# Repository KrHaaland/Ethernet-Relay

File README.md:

# Ethernet-Relay
Relay module using ethernet and MQTT

Put togethet with parts i had laying around.

Its based on a Atmega328p using minicore Arduino bootloader, running at 8Mhz at 3.3 volts.

Ethernet is a W5500-module brought from aliexpress, a 24LC512 for storing the web-interface, FT232 for communicating via usb and updating FW.

The mqtt topic postfix is "/relay1/set" and "/relay2/set" for turing the relays on or off, and "/relay1" or "/relay2" for getting the current status of the relays, the staus will be published according to update time set in the web-interface.

PCB is drawn in Kicad and the casing is draw using solidworks and printed on a Prusa mini+ 3D-Printer.
The print has inserts melted in place to have threads, used for fasten pcb and the back lid.

Some Instructions, the external EEPROM is written by a seperate program, since the controller is to small to contain the web page while running the primary program. When the EEPROM is written the primary program is uploaded and are using the data on the EEPROM to send the web page to a web-client request.

The FT232 is default set to 100mA, this might not be a problem if the device is powered by a charger, but beeing powered by the USB of a computer 100mA is not enough to power the ethernet or relays, this is solved using [FT_PROG](https://ftdichip.com/utilities/) to configure the FT232 to be able to draw up to 500mA.

</br><br></br><br></br><br>

</br><br></br><br></br><br>

</br><br></br><br></br><br>

</br><br></br><br></br><br>

</br><br></br><br></br><br>

</br><br></br><br></br><br>

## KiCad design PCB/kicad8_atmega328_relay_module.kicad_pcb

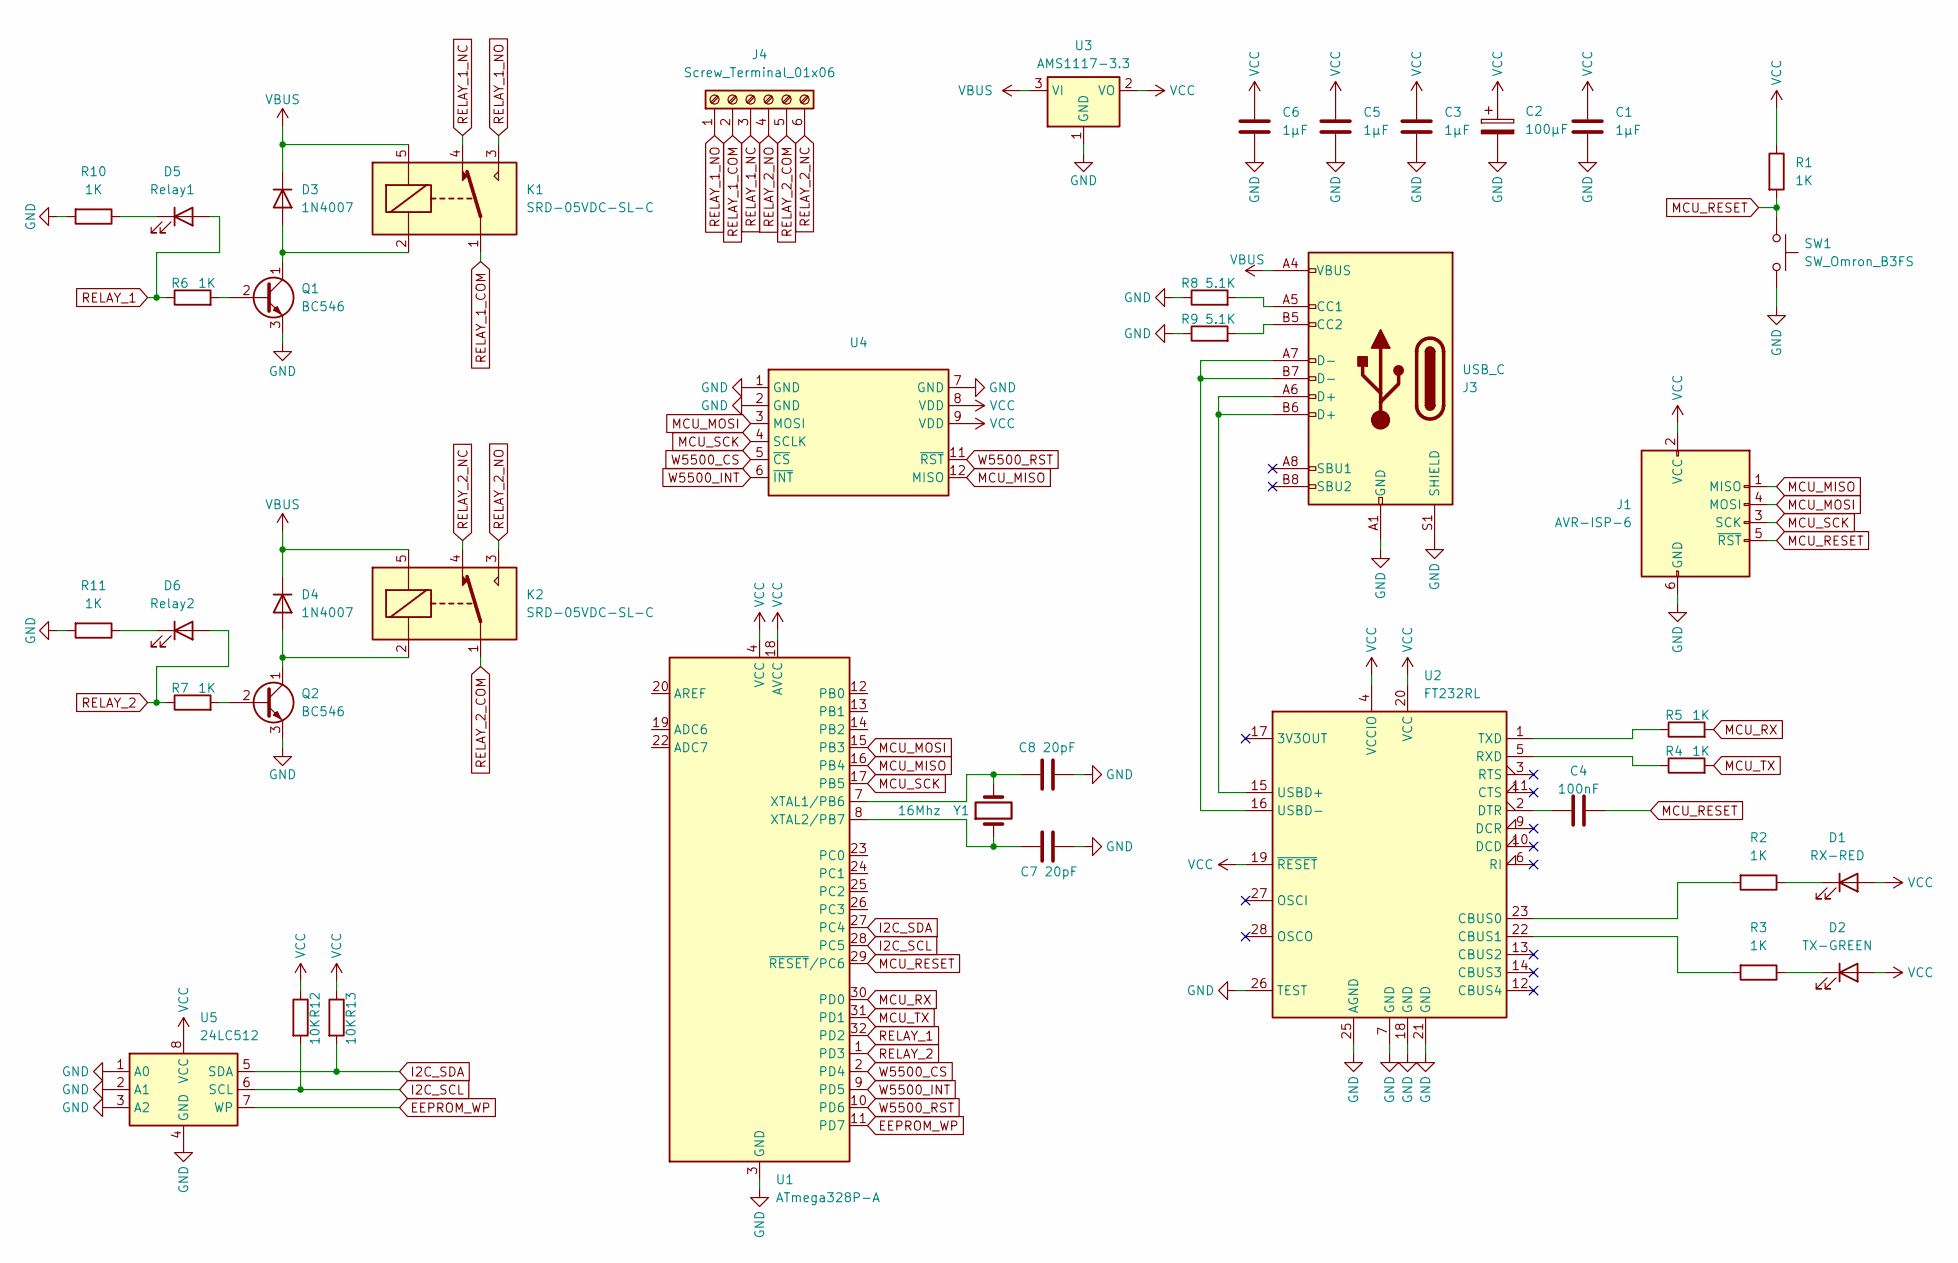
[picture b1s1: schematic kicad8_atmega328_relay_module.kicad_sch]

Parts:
C1, C3, C5, C6: 1µF; C_1206_3216Metric_Pad1.33x1.80mm_HandSolder
C2: 100µF; CP_Elec_5x5.8
C4: 100nF; C_1206_3216Metric_Pad1.33x1.80mm_HandSolder
C7, C8: 20pF; C_1206_3216Metric_Pad1.33x1.80mm_HandSolder
D1: RX-RED; LED_1206_3216Metric_Pad1.42x1.75mm_HandSolder
D2: TX-GREEN; LED_1206_3216Metric_Pad1.42x1.75mm_HandSolder
D3, D4: 1N4007; D_DO-41_SOD81_P7.62mm_Horizontal
D5: Relay1; LED_1206_3216Metric_Pad1.42x1.75mm_HandSolder
D6: Relay2; LED_1206_3216Metric_Pad1.42x1.75mm_HandSolder
J1: AVR-ISP-6; IDC-Header_2x03_P2.54mm_Vertical
J3: USB_C; USB_C_Receptacle_GCT_USB4110
J4: Screw_Terminal_01x06; TerminalBlock_WAGO_804-106_1x06_P5.00mm_45Degree
K1, K2: SRD-05VDC-SL-C; Relay_SPDT_SANYOU_SRD_Series_Form_C
Q1, Q2: BC546; TO-92_Inline
R1, R2, R3, R4, R5, R6, R7, R10, R11: 1K; R_1206_3216Metric_Pad1.30x1.75mm_HandSolder
R8, R9: 5.1K; R_1206_3216Metric_Pad1.30x1.75mm_HandSolder
R12, R13: 10K; R_1206_3216Metric_Pad1.30x1.75mm_HandSolder
SW1: SW_Omron_B3FS; SW_SPST_Omron_B3FS-100xP
U1: ATmega328P-A; TQFP-32_7x7mm_P0.8mm
U2: FT232RL; SSOP-28_5.3x10.2mm_P0.65mm
U3: AMS1117-3.3; SOT-223-3_TabPin2
U4: W5500Mini
U5: 24LC512; SOIC-8_3.9x4.9mm_P1.27mm
Y1: 16Mhz; Crystal_HC49-4H_Vertical

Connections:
EEPROM_WP: U1.11 (PD7), U5.7 (WP)
GND: C1.2, C2.2, C3.2, C5.2, C6.2, C7.2, C8.2, J1.6 (GND), J3.A1 (GND), J3.A12 (GND), J3.B1 (GND), J3.B12 (GND), J3.S1 (SHIELD), Q1.3 (E), Q2.3 (E), R8.1, R9.1, R10.2, R11.2, SW1.2, U1.3 (GND), U1.5 (GND), U1.21 (GND), U2.7 (GND), U2.18 (GND), U2.21 (GND), U2.25 (AGND), U2.26 (TEST), U3.1 (GND), U4.1 (GND), U4.2 (GND), U4.7 (GND), U5.1 (A0), U5.2 (A1), U5.3 (A2), U5.4 (GND)
I2C_SCL: R12.2, U1.28 (PC5), U5.6 (SCL)
I2C_SDA: R13.2, U1.27 (PC4), U5.5 (SDA)
MCU_MISO: J1.1 (MISO), U1.16 (PB4), U4.12 (MISO)
MCU_MOSI: J1.4 (MOSI), U1.15 (PB3), U4.3 (MOSI)
MCU_RESET: C4.1, J1.5 (~RST), R1.2, SW1.1, U1.29 (~RESET/PC6)
MCU_RX: R5.2, U1.30 (PD0)
MCU_SCK: J1.3 (SCK), U1.17 (PB5), U4.4 (SCLK)
MCU_TX: R4.2, U1.31 (PD1)
unnamed: D1.1 (K), R2.1
unnamed: D2.1 (K), R3.1
unnamed: D3.2 (A), K1.2, Q1.1 (C)
unnamed: D4.2 (A), K2.2, Q2.1 (C)
unnamed: D5.1 (K), R10.1
unnamed: D6.1 (K), R11.1
unnamed: J3.A5 (CC1), R8.2
unnamed: J3.B5 (CC2), R9.2
unnamed: Q1.2 (B), R6.2
unnamed: Q2.2 (B), R7.2
unnamed: C8.1, U1.7 (XTAL1/PB6), Y1.2
unnamed: C7.1, U1.8 (XTAL2/PB7), Y1.1
unnamed: R2.2, U2.23 (CBUS0)
unnamed: R3.2, U2.22 (CBUS1)
unnamed: C4.2, U2.2 (DTR)
unnamed: R4.1, U2.5 (RXD)
unnamed: R5.1, U2.1 (TXD)
RELAY_1: D5.2 (A), R6.1, U1.32 (PD2)
RELAY_1_COM: J4.2, K1.1
RELAY_1_NC: J4.3, K1.4
RELAY_1_NO: J4.1, K1.3
RELAY_2: D6.2 (A), R7.1, U1.1 (PD3)
RELAY_2_COM: J4.5, K2.1
RELAY_2_NC: J4.6, K2.4
RELAY_2_NO: J4.4, K2.3
USB_D+: J3.A6 (D+), J3.B6 (D+), U2.15 (USBD+)
USB_D-: J3.A7 (D-), J3.B7 (D-), U2.16 (USBD-)
VBUS: D3.1 (K), D4.1 (K), J3.A4 (VBUS), J3.A9 (VBUS), J3.B4 (VBUS), J3.B9 (VBUS), K1.5, K2.5, U3.3 (VI)
VCC: C1.1, C2.1, C3.1, C5.1, C6.1, D1.2 (A), D2.2 (A), J1.2 (VCC), R1.1, R12.1, R13.1, U1.4 (VCC), U1.6 (VCC), U1.18 (AVCC), U2.4 (VCCIO), U2.19 (~RESET), U2.20 (VCC), U3.2 (VO), U4.8 (VDD), U4.9 (VDD), U5.8 (VCC)
W5500_CS: U1.2 (PD4), U4.5 (~CS)
W5500_INT: U1.9 (PD5), U4.6 (~INT)
W5500_RST: U1.10 (PD6), U4.11 (~RST)

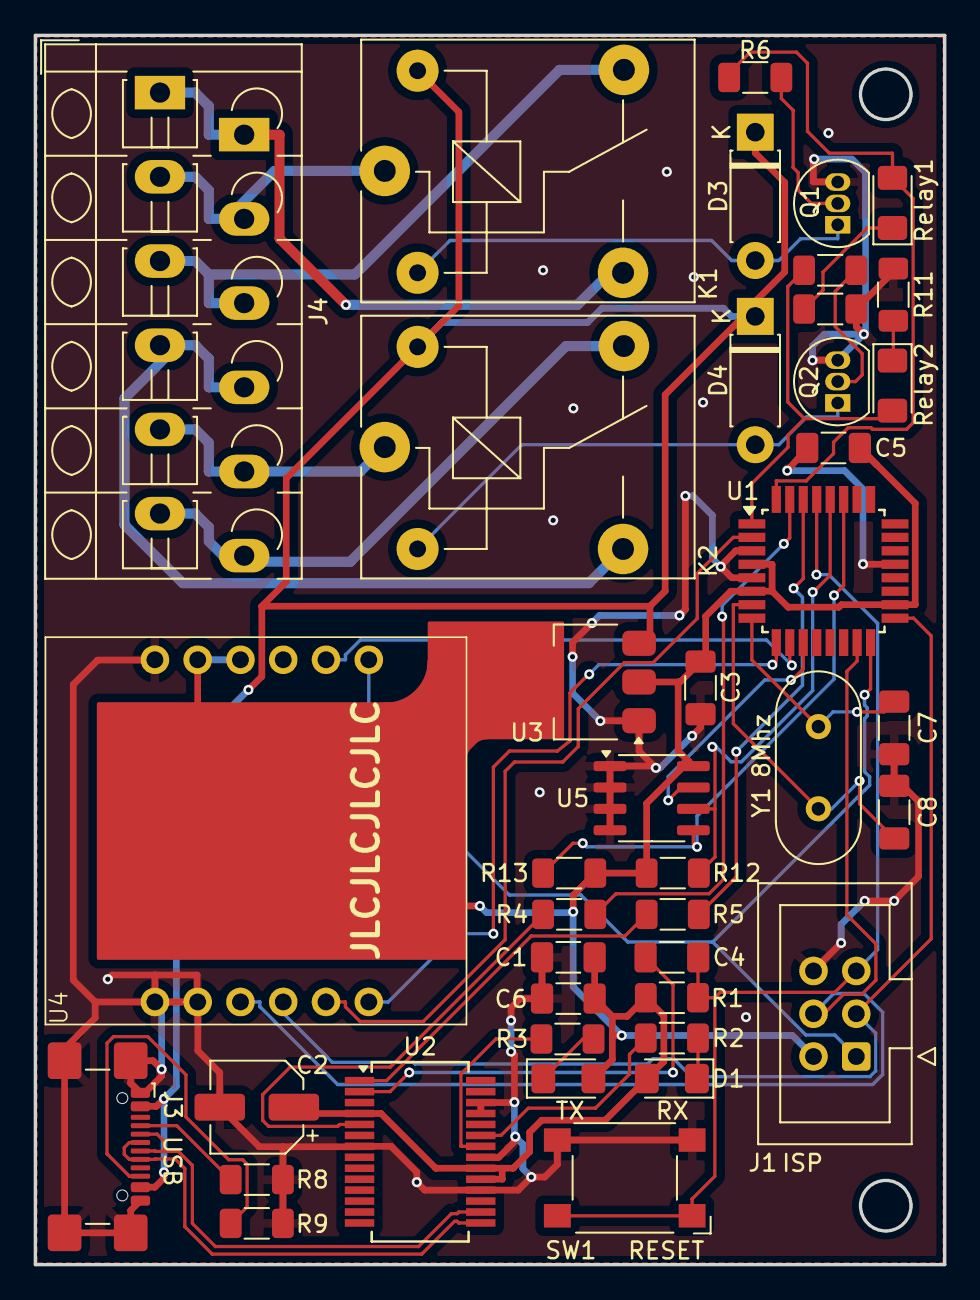
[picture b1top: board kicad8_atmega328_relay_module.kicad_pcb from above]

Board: 2 copper layers, 54.0 x 73.0 mm, 41 parts (0 on the bottom side), 42 nets.

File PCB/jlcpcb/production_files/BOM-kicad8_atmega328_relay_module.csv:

Comment,Designator,Footprint,LCSC
1µF,C5,C_1206_3216Metric_Pad1.33x1.80mm_HandSolder,
16Mhz,Y1,Crystal_HC49-4H_Vertical,
SW_Omron_B3FS,SW1,SW_SPST_Omron_B3FS-100xP,
1K,R4,R_1206_3216Metric_Pad1.30x1.75mm_HandSolder,
SRD-05VDC-SL-C,K1,Relay_SPDT_SANYOU_SRD_Series_Form_C,
100µF,C2,CP_Elec_5x5.8,
1K,R1,R_1206_3216Metric_Pad1.30x1.75mm_HandSolder,
20pF,C8,C_1206_3216Metric_Pad1.33x1.80mm_HandSolder,
AVR-ISP-6,J1,IDC-Header_2x03_P2.54mm_Vertical,
ATmega328P-A,U1,TQFP-32_7x7mm_P0.8mm,
5.1K,R9,R_1206_3216Metric_Pad1.30x1.75mm_HandSolder,
1K,R5,R_1206_3216Metric_Pad1.30x1.75mm_HandSolder,
1N4007,D3,D_DO-41_SOD81_P7.62mm_Horizontal,
BC546,Q2,TO-92_Inline,
1µF,C1,C_1206_3216Metric_Pad1.33x1.80mm_HandSolder,
USB_C,J3,USB_C_Receptacle_GCT_USB4110,
100nF,C4,C_1206_3216Metric_Pad1.33x1.80mm_HandSolder,
1K,R2,R_1206_3216Metric_Pad1.30x1.75mm_HandSolder,
1µF,C6,C_1206_3216Metric_Pad1.33x1.80mm_HandSolder,
AMS1117-3.3,U3,SOT-223-3_TabPin2,
20pF,C7,C_1206_3216Metric_Pad1.33x1.80mm_HandSolder,
5.1K,R8,R_1206_3216Metric_Pad1.30x1.75mm_HandSolder,
RX-RED,D1,LED_1206_3216Metric_Pad1.42x1.75mm_HandSolder,
1K,R7,R_1206_3216Metric_Pad1.30x1.75mm_HandSolder,
1N4007,D4,D_DO-41_SOD81_P7.62mm_Horizontal,
TX-GREEN,D2,LED_1206_3216Metric_Pad1.42x1.75mm_HandSolder,
SRD-05VDC-SL-C,K2,Relay_SPDT_SANYOU_SRD_Series_Form_C,
~,U4,W5500Mini,
BC546,Q1,TO-92_Inline,
1µF,C3,C_1206_3216Metric_Pad1.33x1.80mm_HandSolder,
Screw_Terminal_01x06,J4,TerminalBlock_WAGO_804-106_1x06_P5.00mm_45Degree,
1K,R6,R_1206_3216Metric_Pad1.30x1.75mm_HandSolder,
1K,R3,R_1206_3216Metric_Pad1.30x1.75mm_HandSolder,
FT232RL,U2,SSOP-28_5.3x10.2mm_P0.65mm,
10K,R13,R_1206_3216Metric_Pad1.30x1.75mm_HandSolder,
1K,R10,R_1206_3216Metric_Pad1.30x1.75mm_HandSolder,
24LC512,U5,SOIC-8_3.9x4.9mm_P1.27mm,
Relay1,D5,LED_1206_3216Metric_Pad1.42x1.75mm_HandSolder,
10K,R12,R_1206_3216Metric_Pad1.30x1.75mm_HandSolder,
Relay2,D6,LED_1206_3216Metric_Pad1.42x1.75mm_HandSolder,
1K,R11,R_1206_3216Metric_Pad1.30x1.75mm_HandSolder,

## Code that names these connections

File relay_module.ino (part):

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// BE SURE TO ALSO CHANGE MQTT CLIENT ID and serial output !!
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#define W5500_CS   PIN_PD4
#define W5500_RST  PIN_PD6

//relays
#define RELAY1PIN PIN_PD2
#define RELAY2PIN PIN_PD3

// Initialize the Ethernet server
EthernetServer server(80);
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/* USED WITH SPI-EEPROM
  // init External EEPROM
  pinMode(EEPROM_CS_PIN, OUTPUT);
  pinMode(EEPROM_WP_PIN, OUTPUT);
  digitalWrite(EEPROM_CS_PIN, HIGH);
  digitalWrite(EEPROM_WP_PIN, LOW);
*/

  // Configure the W5500 reset pin
  pinMode(W5500_RST, OUTPUT);
  digitalWrite(W5500_RST, HIGH); // Keep reset pin high

  Ethernet.init(W5500_CS);

  // Reset the W5500 Ethernet module
  digitalWrite(W5500_RST, LOW); // Set reset pin low
  delay(50);                    // Hold low for 50ms
  digitalWrite(W5500_RST, HIGH); // Set reset pin high


  // check if DHCP is selected and init network
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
